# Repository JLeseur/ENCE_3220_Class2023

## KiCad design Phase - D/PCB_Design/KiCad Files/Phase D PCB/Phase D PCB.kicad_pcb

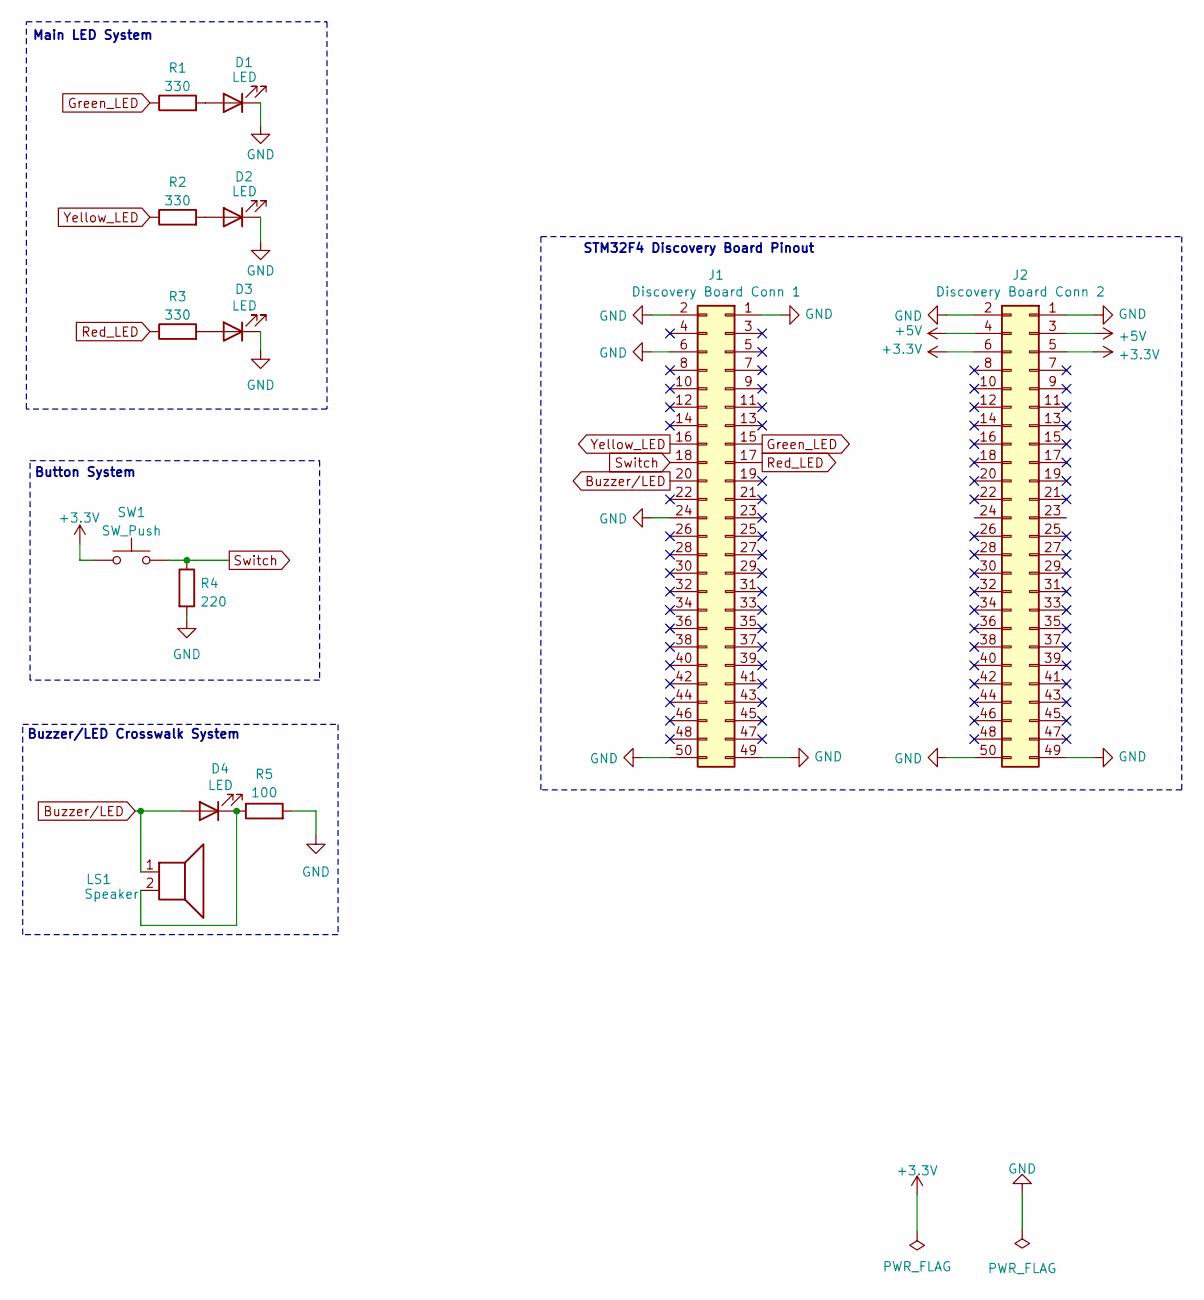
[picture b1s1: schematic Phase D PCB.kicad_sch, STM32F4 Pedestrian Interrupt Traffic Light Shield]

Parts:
D1, D2, D3, D4: LED; LED_D5.0mm_Clear
J1: Discovery Board Conn 1; PinSocket_2x25_P2.54mm_Vertical
J2: Discovery Board Conn 2; PinSocket_2x25_P2.54mm_Vertical
LS1: Speaker; Buzzer_12x9.5RM7.6
R1, R2, R3: 330; R_Axial_DIN0207_L6.3mm_D2.5mm_P10.16mm_Horizontal
R4: 220; R_Axial_DIN0207_L6.3mm_D2.5mm_P10.16mm_Horizontal
R5: 100; R_Axial_DIN0207_L6.3mm_D2.5mm_P10.16mm_Horizontal
SW1: SW_Push; SW_PUSH_6mm

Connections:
+3V0: J2.5, J2.6, SW1.1
+5V: J2.3, J2.4
Buzzer/LED: D4.2 (A), J1.20, LS1.1
GND: D1.1 (K), D2.1 (K), D3.1 (K), J1.1, J1.2, J1.6, J1.24, J1.49, J1.50, J2.1, J2.2, J2.49, J2.50, R4.2, R5.2
Green_LED: J1.15, R1.1
unnamed: D1.2 (A), R1.2
unnamed: D2.2 (A), R2.2
unnamed: D3.2 (A), R3.2
unnamed: D4.1 (K), LS1.2, R5.1
Red_LED: J1.17, R3.1
Switch: J1.18, R4.1, SW1.2
Yellow_LED: J1.16, R2.1

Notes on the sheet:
Main LED System
Buzzer/LED Crosswalk System
Button System
STM32F4 Discovery Board Pinout

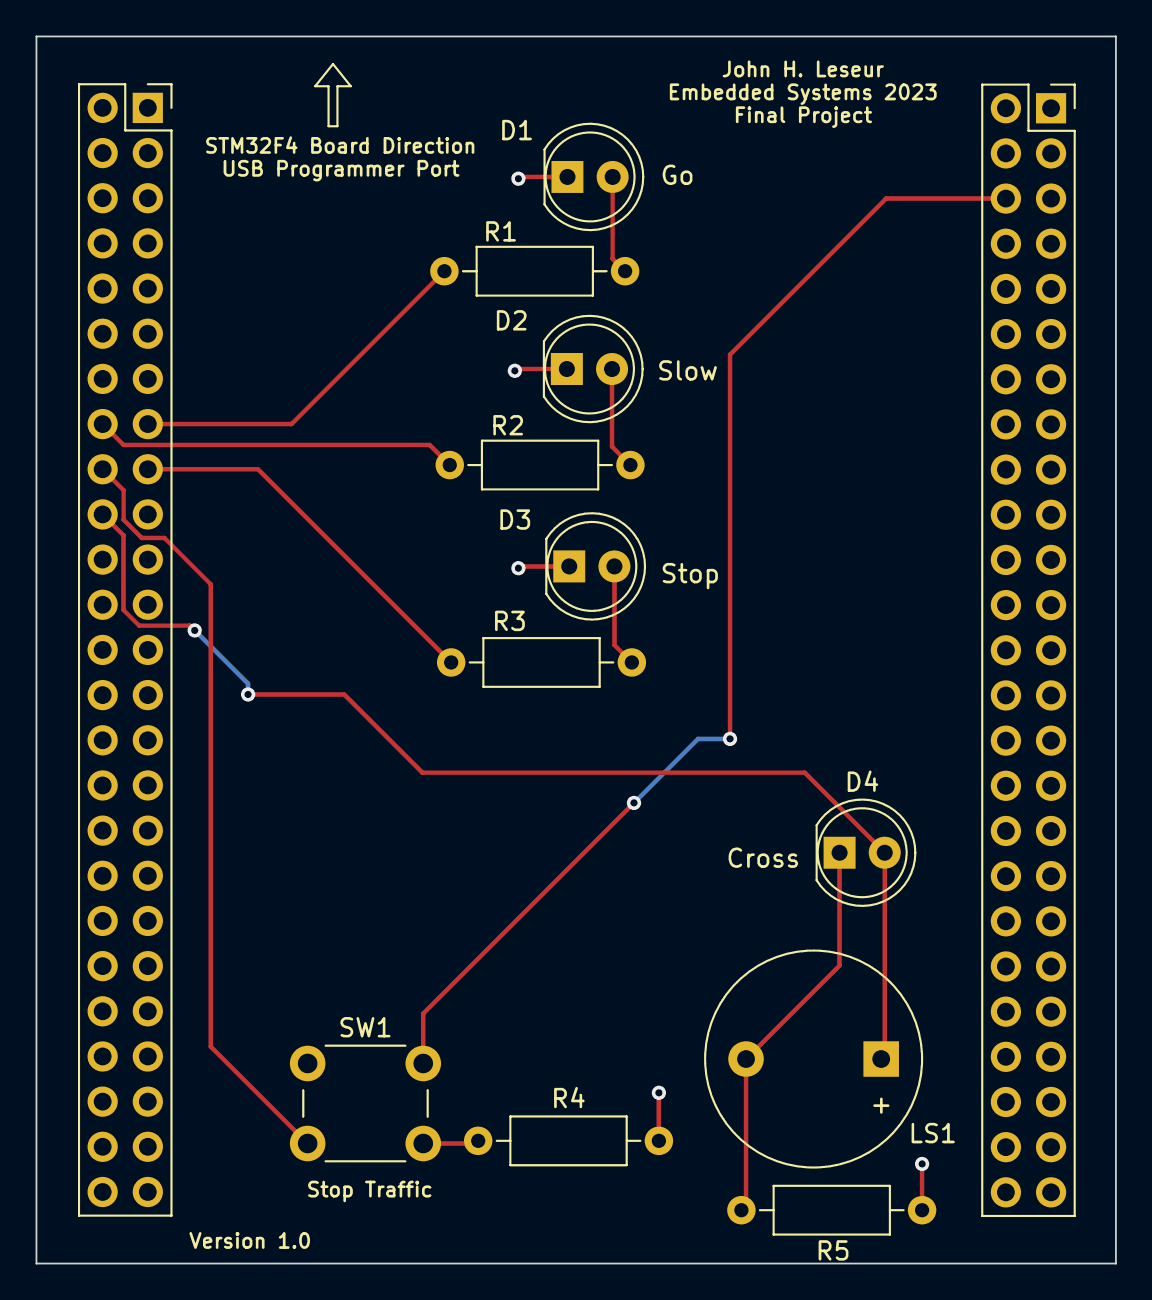
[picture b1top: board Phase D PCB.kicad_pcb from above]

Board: 2 copper layers, 60.7 x 69.0 mm, 13 parts (0 on the bottom side), 12 nets.

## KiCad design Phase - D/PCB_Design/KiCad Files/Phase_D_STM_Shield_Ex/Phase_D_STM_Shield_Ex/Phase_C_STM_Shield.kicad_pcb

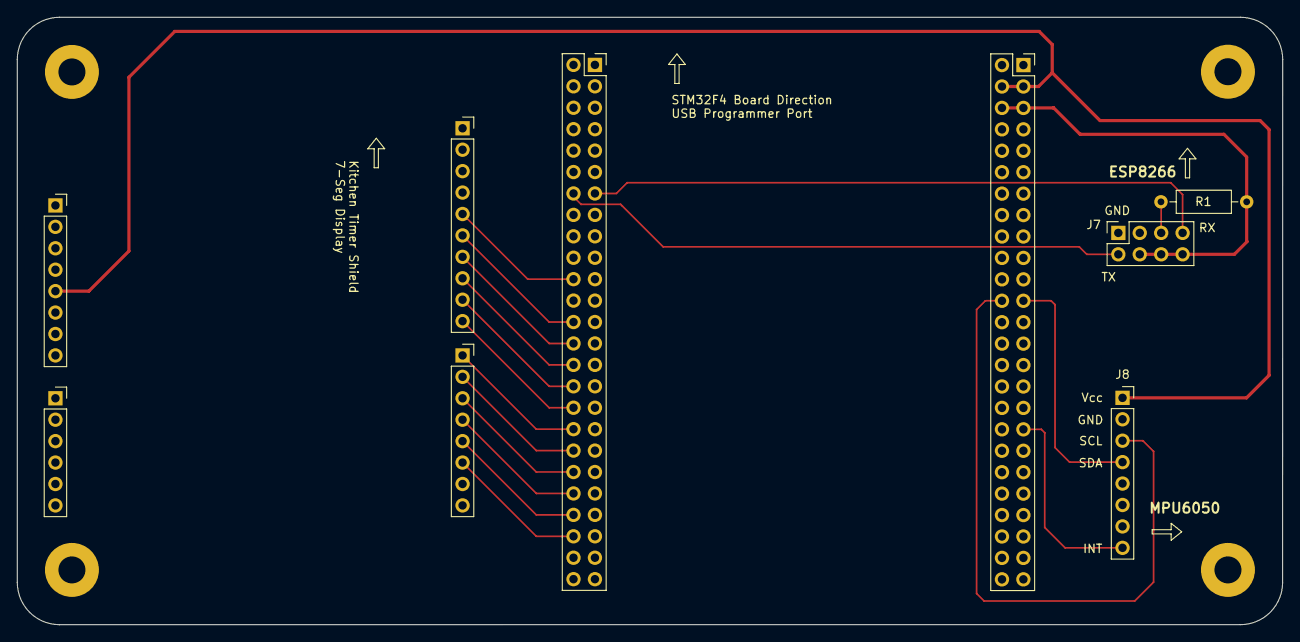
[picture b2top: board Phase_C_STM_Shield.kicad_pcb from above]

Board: 2 copper layers, 150.0 x 72.0 mm, 13 parts (0 on the bottom side), 21 nets.

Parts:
H1, H2, H3, H4: MountingHole; MountingHole_3.2mm_M3_Pad
J1: Discovery Board Conn 1; PinSocket_2x25_P2.54mm_Vertical
J2: Discovery Board Conn 2; PinSocket_2x25_P2.54mm_Vertical
J3: Power; PinSocket_1x08_P2.54mm_Vertical
J4: Analog; PinSocket_1x06_P2.54mm_Vertical
J5: Digital/PWM; PinSocket_1x10_P2.54mm_Vertical
J6: Digital/PWM; PinSocket_1x08_P2.54mm_Vertical
J7: ESP_Conn; PinSocket_2x04_P2.54mm_Vertical
J8: MPU6050_Conn; PinSocket_1x08_P2.54mm_Vertical
R1: 10k; R_Axial_DIN0207_L6.3mm_D2.5mm_P10.16mm_Horizontal

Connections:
+3V0: J2.5, J2.6, J7.4, J7.6, J7.8, R1.1
+5V: J2.3, J2.4, J3.5, J8.1
Button_1: J1.46, J6.6
Button_2: J1.44, J6.5
Buzzer: J1.38, J6.2
DS: J1.32, J5.9
Dig1: J1.22, J5.5
Dig2: J1.26, J5.6
Dig3: J1.28, J5.7
Dig4: J1.30, J5.8
GND: J1.1, J1.2, J1.6, J1.24, J1.49, J1.50, J2.1, J2.2, J2.49, J2.50, J3.6, J3.7, J5.4, J7.1, J8.2
GREEN_LED: J1.42, J6.4
INT: J2.35, J8.8
unnamed: J7.5, R1.2
RED_LED: J1.40, J6.3
RX: J1.13, J7.7
SCL: J2.24, J8.3
SDA: J2.23, J8.4
SH_CP: J1.36, J6.1
ST_CP: J1.34, J5.10
TX: J1.14, J7.2

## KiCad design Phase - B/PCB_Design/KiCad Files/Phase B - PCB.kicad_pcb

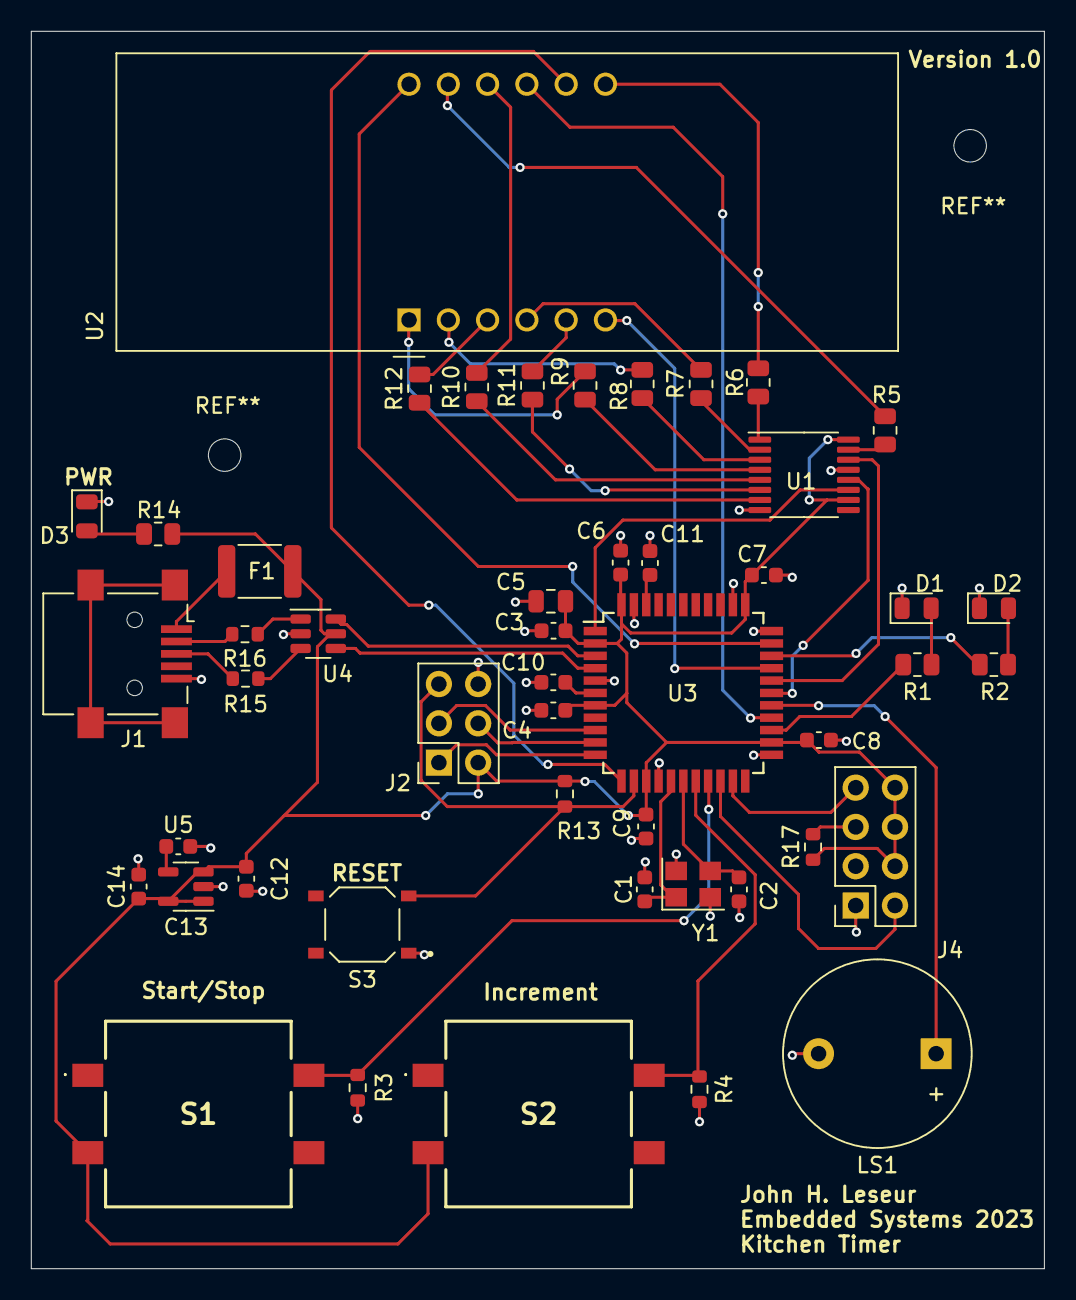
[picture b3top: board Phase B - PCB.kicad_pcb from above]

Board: 2 copper layers, 65.5 x 80.0 mm, 48 parts (0 on the bottom side), 52 nets.

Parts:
C1, C2: 22pF; C_0603_1608Metric
C3, C4, C6, C7, C8, C9, C11: 0.1uF; C_0603_1608Metric
C5: 10uF; C_0805_2012Metric
C10, C12: 1uF; C_0603_1608Metric
C13: 10nF; C_0603_1608Metric
C14: 2.2uF; C_0603_1608Metric
D1, D2, D3: LED; LED_0805_2012Metric
F1: PTCSMD; Fuse_1812_4532Metric
J1: USB_B_Mini; USB_Mini-B_Lumberg_2486_01_Horizontal
J2: AVR-ISP-6; PinSocket_2x03_P2.54mm_Vertical
J4: ESP_Conn; PinSocket_2x04_P2.54mm_Vertical
LS1: Speaker; Buzzer_12x9.5RM7.6
R1, R2: 330; R_0805_2012Metric
R3, R4, R13, R17: 10k; R_0603_1608Metric
R5, R6, R7, R8, R9, R10, R11, R12: 100; R_0805_2012Metric
R14: 1k; R_0805_2012Metric
R15, R16: 22; R_0603_1608Metric
S1, S2: PTS125SM43SMTR21M_LFS; PTS125_SMD_Button
S3: PTS526_SM08_SMTR2_LFS; PTS526_SMD_Button
U1: 74HC595; TSSOP-16_4.4x5mm_P0.65mm
U2: CA56-12EWA
U3: ATmega32U4-A; TQFP-44_10x10mm_P0.8mm
U4: USBLC6-2SC6; SOT-23-6
U5: LP2985-3.3; SOT-23-5
Y1: 16MHz; Crystal_SMD_Abracon_ABM8G-4Pin_3.2x2.5mm

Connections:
/AREF: C11.1, U3.42 (AREF)
/UCAP: C10.1, U3.6 (UCAP)
BUTTON_1: R3.1, S1.B1 (NO_2), U3.19 (PD1)
BUTTON_2: R4.1, S2.B1 (NO_2), U3.18 (PD0)
BUZZER: LS1.1, U3.27 (PD7)
DS: U1.14 (SER), U3.29 (PB5)
Dig1: U2.12 (CA1), U3.32 (PC7)
Dig2: U2.9 (CA2), U3.26 (PD6)
Dig3: U2.8 (CA3), U3.12 (PB7)
Dig4: U2.6 (CA4), U3.30 (PB6)
GND: C1.2, C2.2, C3.2, C4.2, C5.2, C6.2, C7.2, C8.2, C9.2, C10.2, C11.2, C12.2, C13.2, C14.2, D1.1 (K), D2.1 (K), D3.1 (K), J1.5 (GND), J2.6 (GND), J4.1, LS1.2, R3.2, R4.2, S3.1, U1.8 (GND), U1.13 (~OE), U3.5 (UGND), U3.15 (GND), U3.23 (GND), U3.33 (~HWB/PE2), U3.35 (GND), U3.43 (GND), U4.2 (GND), U5.2 (GND), Y1.2, Y1.4
GREEN_LED: R1.1, U3.25 (PD4)
MISO: J2.1 (MISO), U3.11 (PB3)
MOSI: J2.4 (MOSI), U3.10 (PB2)
unnamed: D1.2 (A), R1.2
unnamed: D2.2 (A), R2.2
unnamed: D3.2 (A), R14.2
unnamed: J1.3 (D+), R15.2
unnamed: J1.2 (D-), R16.2
unnamed: F1.1, J1.1 (VBUS)
unnamed: J4.5, R17.2
unnamed: R12.2, U2.3 (DPX)
unnamed: R5.2, U2.11 (a)
unnamed: R6.2, U2.7 (b)
unnamed: R7.2, U2.4 (c)
unnamed: R8.2, U2.2 (d)
unnamed: R9.2, U2.1 (e)
unnamed: R10.2, U2.10 (f)
unnamed: R11.2, U2.5 (g)
unnamed: C13.1, U5.4 (BP)
RED_LED: R2.1, U3.31 (PC6)
RESET: J2.5 (~RST), R13.2, S3.3, U3.13 (~RESET)
RX: J4.7, U3.21 (PD3)
SCK: J2.3 (SCK), U3.9 (PB1)
SH_CP: U1.11 (SRCLK), U3.1 (PE6)
ST_CP: U1.12 (RCLK), U3.28 (PB4)
TX: J4.2, U3.20 (PD2)
USB_CONN_D+: R15.1, U4.3 (I/O2)
USB_CONN_D-: R16.1, U4.1 (I/O1)
USB_D+: U3.4 (D+), U4.4 (I/O2)
USB_D-: U3.3 (D-), U4.6 (I/O1)
VCC: C3.1, C4.1, C5.1, C6.1, C7.1, C8.1, C9.1, C12.1, C14.1, F1.2, J2.2 (VCC), J4.4, J4.6, J4.8, R13.1, R14.1, R17.1, S1.C1 (COM_1), S2.C1 (COM_1), U1.10 (~SRCLR), U1.16 (VCC), U3.2 (UVCC), U3.7 (VBUS), U3.14 (VCC), U3.24 (AVCC), U3.34 (VCC), U3.44 (AVCC), U4.5 (VBUS), U5.1 (VIN), U5.3 (ON/~OFF), U5.5 (VOUT)
XTAL1: C2.1, U3.17 (XTAL1), Y1.3
XTAL2: C1.1, U3.16 (XTAL2), Y1.1
a: R5.1, U1.15 (QA)
b: R6.1, U1.1 (QB)
c: R7.1, U1.2 (QC)
d: R8.1, U1.3 (QD)
dp: R12.1, U1.7 (QH)
e: R9.1, U1.4 (QE)
f: R10.1, U1.5 (QF)
g: R11.1, U1.6 (QG)

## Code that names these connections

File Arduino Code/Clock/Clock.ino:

#define BUTTON_1  2
#define BUTTON_2  3
#define GREEN_LED 4
#define RED_LED   5
#define BUZZER    6

#define DATA      9
#define LATCH     8
#define CLOCK     7

#define DIGIT_4   10
#define DIGIT_3   11
#define DIGIT_2   12
#define DIGIT_1   13

unsigned char table[]=
{0x3f,0x06,0x5b,0x4f,0x66,0x6d,0x7d,0x07,0x7f,0x6f,0x77,0x7c,0x39,0x5e,0x79,0x71,0x00};

volatile unsigned char onescount = 0;
volatile unsigned char tenscount = 0;


volatile unsigned char isr_1_flag = 0;
volatile unsigned char isr_2_flag = 0;
 
 void setup() {
  // LEDs Pins
  pinMode(RED_LED, OUTPUT);
  pinMode(GREEN_LED, OUTPUT);

  // Button Pins
  pinMode(BUTTON_1, INPUT_PULLUP);
  attachInterrupt(digitalPinToInterrupt(BUTTON_1), Button_1_ISR, RISING);
  pinMode(BUTTON_2, INPUT_PULLUP);
  attachInterrupt(digitalPinToInterrupt(BUTTON_2), Button_2_ISR, RISING);

  // Buzer Pins
  pinMode(BUZZER, OUTPUT);

  // 7-Seg Display
  pinMode(DIGIT_1, OUTPUT);
  pinMode(DIGIT_2, OUTPUT);
  pinMode(DIGIT_3, OUTPUT);
  pinMode(DIGIT_4, OUTPUT);

  // Shift Register Pins
  pinMode(LATCH, OUTPUT);
  pinMode(CLOCK, OUTPUT);
  pinMode(DATA, OUTPUT);

}

void Display(int digit, unsigned char num)
{
  disp_on(digit);
  digitalWrite(LATCH, LOW);
  shiftOut(DATA, CLOCK, MSBFIRST, table[num);
  digitalWrite(LATCH, HIGH);
}

void Active_Buzzer()
{
  unsigned char i;
  unsigned char sleep_time = 1; // ms
  
  for (i=0; i<100; i++)
   {
    digitalWrite(BUZZER,HIGH);
    delay(sleep_time);//wait for 1ms
    digitalWrite(BUZZER,LOW);
    delay(sleep_time);//wait for 1ms
    }
}

void FlashLEDs() {
  digitalWrite(GREEN_LED, LOW);
  digitalWrite(RED_LED, LOW);
  delay(150);
  digitalWrite(GREEN_LED, HIGH);
  digitalWrite(RED_LED, HIGH);
}

void Countdown()
{
  while(onescount != 0) {
    onescount--;
    delay(1000);
    Display(10, onescount);
  }
  /*
    if (onescount == 0) {
      for (int i = 0; i < 3; i++){
      FlashLEDs();
      Active_Buzzer();
      delay(25);
      Active_Buzzer();
      delay(50);
      Active_Buzzer();
      delay(25);
    }
    */
}

void Count() {
  Display(10, onescount);
  onescount++;
  delay(10);
  if(onescount == 9) {
    onescount = 0;
    tenscount++;
    Display(11, tenscount);
  }
}

void disp_on(int digit)
{
   digitalWrite(DIGIT_1, HIGH);
   digitalWrite(DIGIT_2, HIGH);
   digitalWrite(DIGIT_3, HIGH);
   digitalWrite(DIGIT_4, HIGH);
   digitalWrite(digit, LOW);
}

void Button_1_ISR()
{
  unsigned int buttonState = 0;  // variable for reading the pushbutton status

  // Set ISR Flag
  isr_1_flag = 1;

  buttonState = digitalRead(BUTTON_1);
  digitalWrite(RED_LED, buttonState);

  Count();
}

void Button_2_ISR()
{ 
  unsigned int buttonState = 0;  // variable for reading the pushbutton status

  // Set ISR Flag
  isr_2_flag = 1;
  
  buttonState = digitalRead(BUTTON_2);
  digitalWrite(GREEN_LED, buttonState);
}

void loop() {
  if(isr_2_flag == 1) {
    isr_2_flag = 0;
    Countdown();
  }
}

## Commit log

2023-04-10 All Arduino Code, PCB Design, and Notes
2023-04-13 Revert "Create Block Diagrams - Phase A.pdf"
    This reverts commit d30276214858cafad6582986df125da5e3d4eb84.
2023-04-13 Block Diagrams - Phase A
2023-04-13 ENCE 3220 - Phase A
2023-04-13 ENCE_3220 - Phase A
2023-04-20 ENCE_3220 - Phase B
2023-05-31 Phase - B
2023-05-31 Phase D - Embedded Systems
